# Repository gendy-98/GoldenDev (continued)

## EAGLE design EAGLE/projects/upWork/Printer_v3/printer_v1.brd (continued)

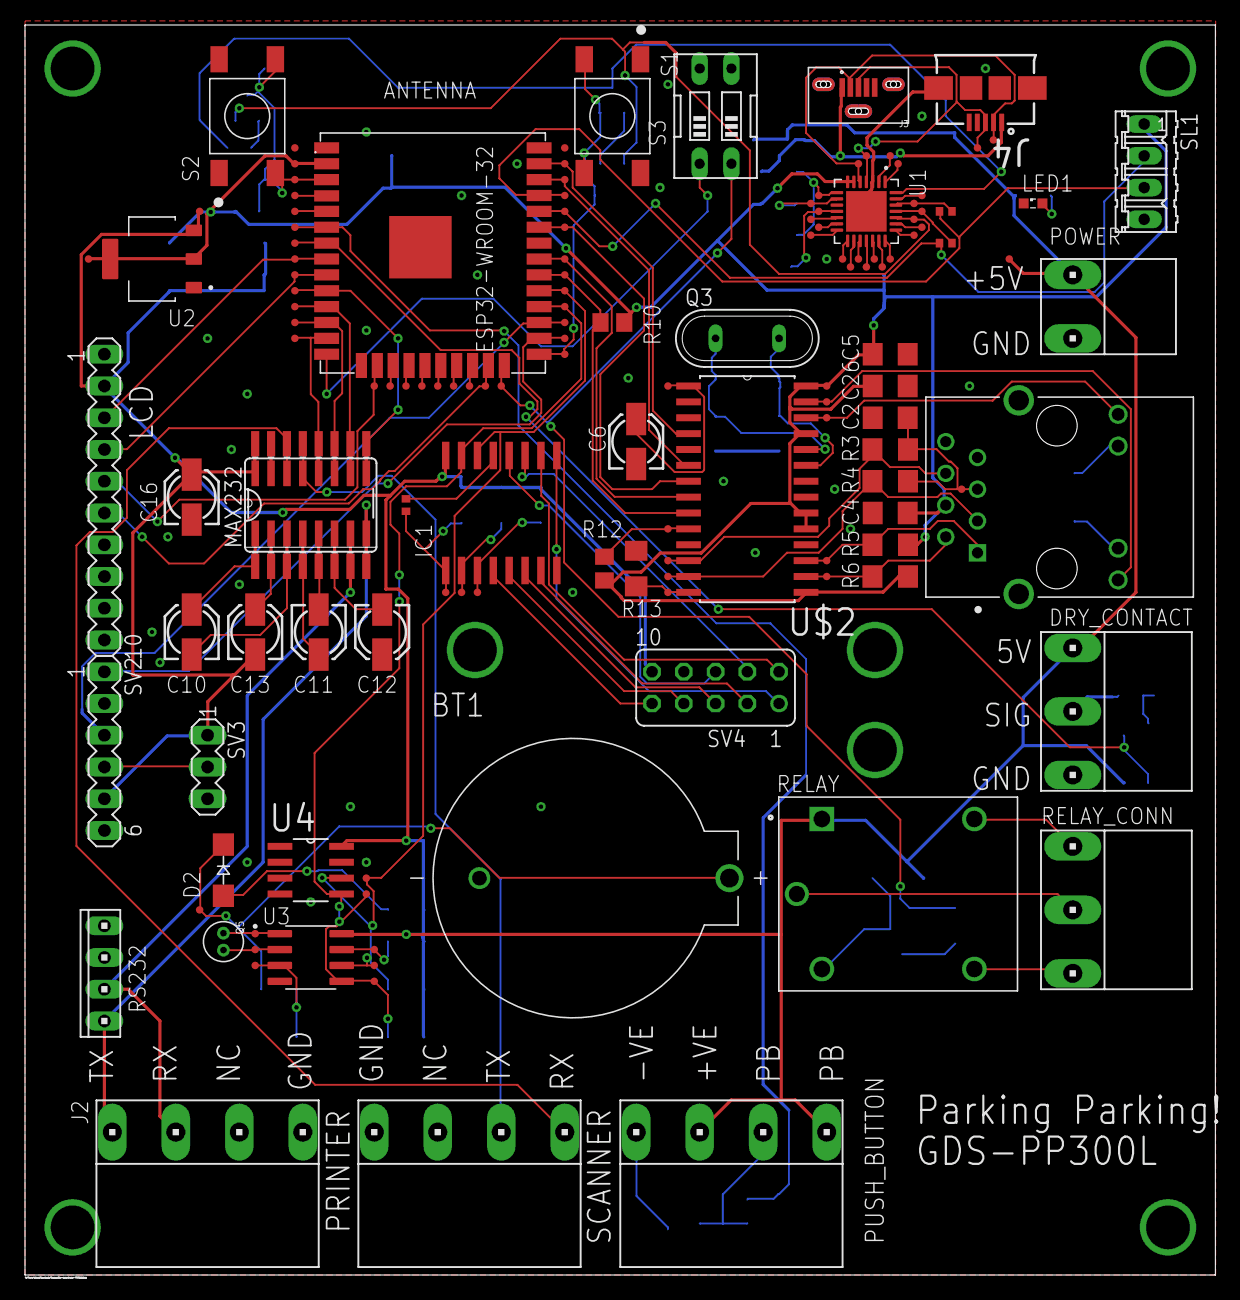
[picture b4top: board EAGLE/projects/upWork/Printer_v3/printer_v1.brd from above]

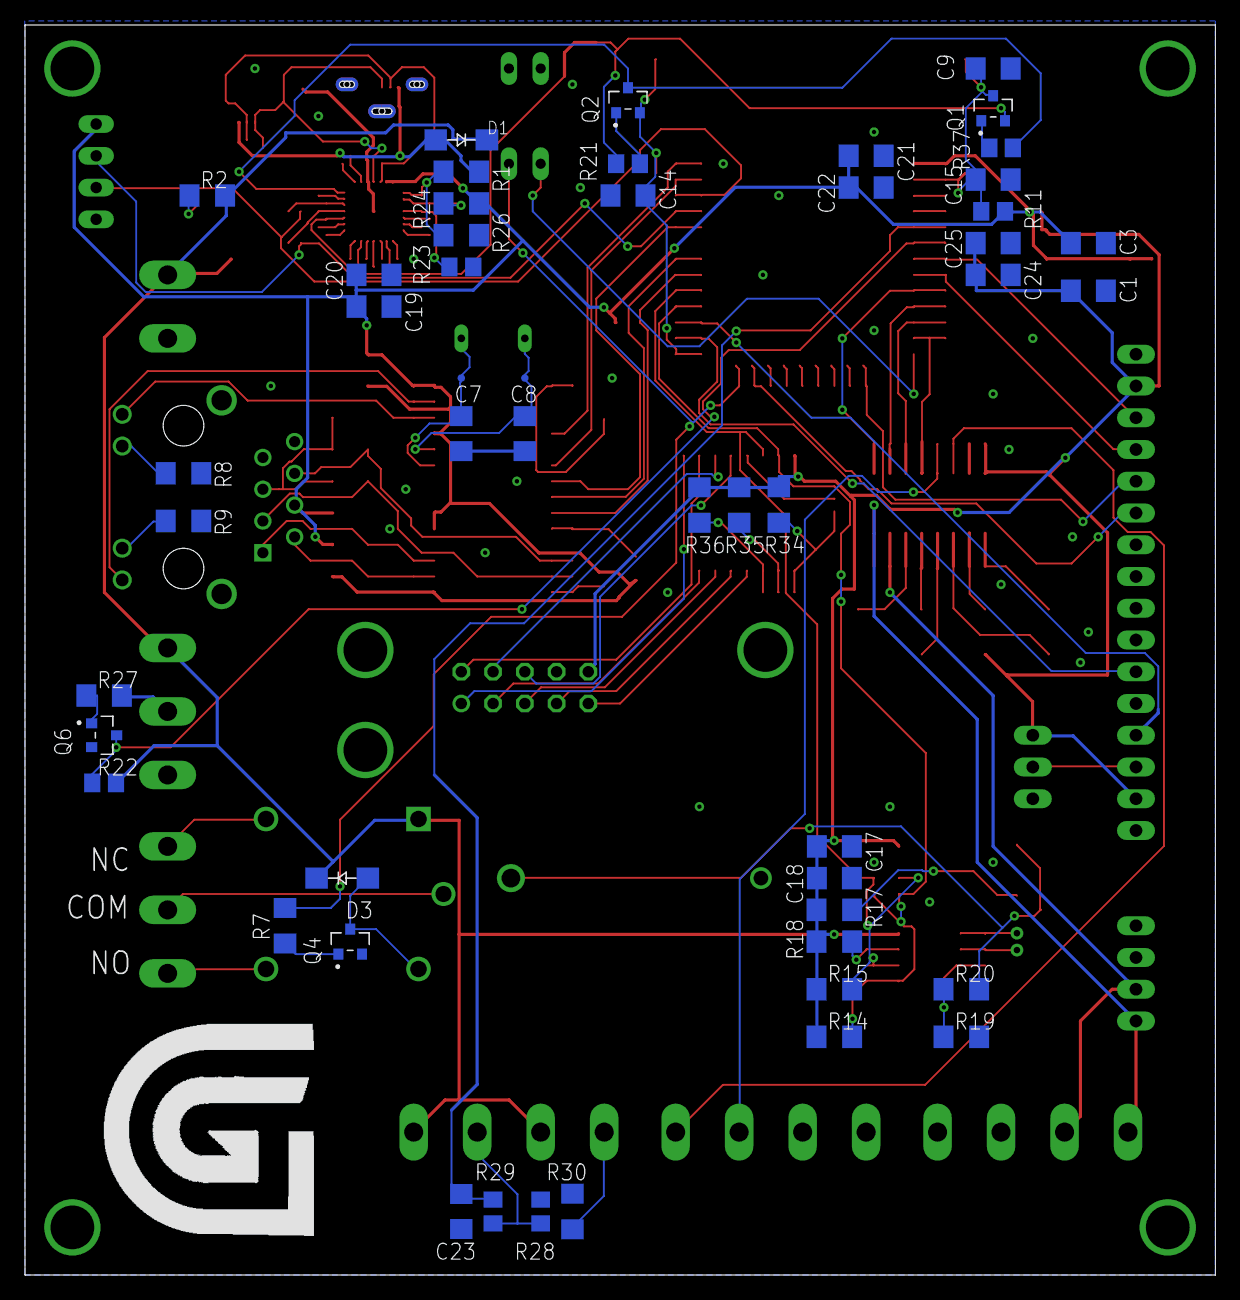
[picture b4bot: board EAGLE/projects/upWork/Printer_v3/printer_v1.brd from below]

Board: 2 copper layers, 95.2 x 100.0 mm, 188 parts (49 on the bottom side), 116 nets.

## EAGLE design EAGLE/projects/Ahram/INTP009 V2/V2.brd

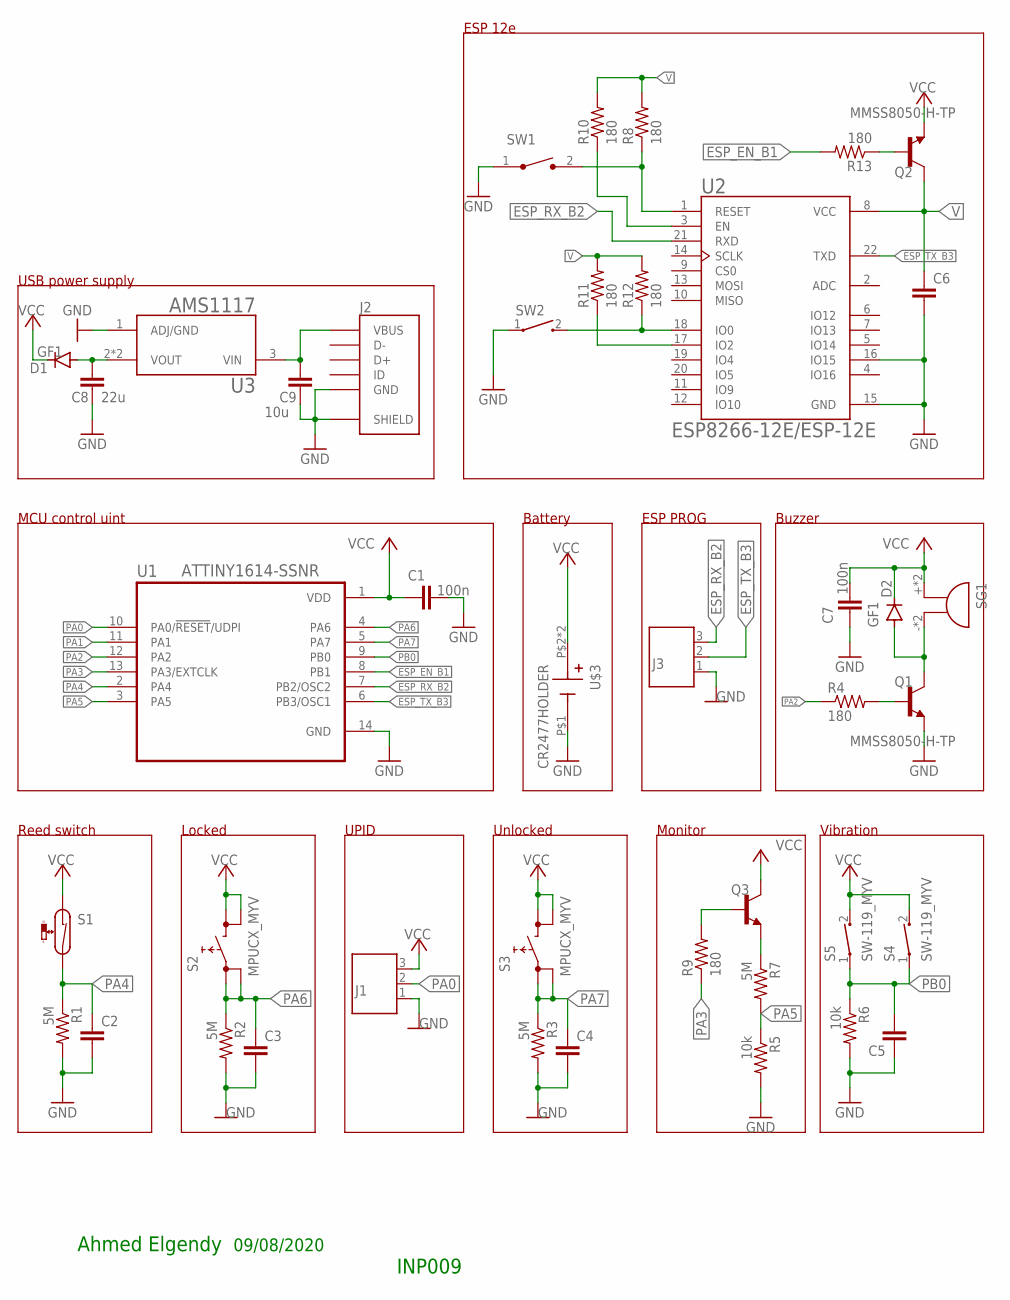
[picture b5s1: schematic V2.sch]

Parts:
C1, C7: 100n; C0805K
C2, C3, C4, C5, C6: C-EUC0805K; C0805K
C8: 22u; C0805K
C9: 10u; C0805K
D1, D2: GF1; SMA-DO214AC
J1, J3: 691508110303
J2: USB3065-XX-00-A_REVE; GCT_USB3065-XX-00-A_REVE
Q1, Q2, Q3: MMSS8050-H-TP; TRANS_MMSS8050-H-TP
R1, R2, R3, R7: 5M; M0805
R4, R8, R9, R10, R11, R12, R13: 180; M0805
R5, R6: 10k; M0805
S1: RI80SMDM-MYV; RI80SMDM-0510-J1
S2, S3: MPUCX_MYV
S4, S5: SW-119_MYV; SW-119
SG1: CMI-9653S-SMT; SMD_BUZZER
SW1: FSMSM; TE_FSMSM
SW2: 1437566-3; SW_1437566-3
U1: ATTINY1614-SSNR; SOIC127P600X175-14N
U2: ESP8266-12E/ESP-12E; XCVR_ESP8266-12E/ESP-12E
U3: AMS1117; SOT229P700X180-4N
U$3: CR2477HOLDER; CR2477

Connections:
ESP_EN_B1: R13.2, U1.8 (PB1)
ESP_RX_B2: J3.3, U1.7 (PB2/OSC2), U2.21 (RXD)
ESP_TX_B3: J3.2, U1.6 (PB3/OSC1), U2.22 (TXD)
GND: C1.2, C2.2, C3.2, C4.2, C5.1, C6.2, C7.1, C8.1, C9.1, J1.1, J2.5 (GND), J2.6 (SHIELD), J2.7 (SHIELD), J2.8 (SHIELD), J2.9 (SHIELD), J3.1, Q1.2 (E), R1.2, R2.2, R3.2, R5.2, R6.2, SW1.1, SW2.1, U1.14 (GND), U2.15 (GND), U2.16 (IO15), U3.1 (ADJ/GND), U$3.P$1 (-)
unnamed: D2.A, Q1.3 (C), SG1.-, SG1.-- (-)
unnamed: C9.2, J2.1 (VBUS), U3.3 (VIN)
unnamed: Q1.1 (B), R4.2
unnamed: C8.2, D1.A, U3.2 (VOUT), U3.4 (VOUT)
unnamed: Q3.1 (B), R9.2
unnamed: Q2.1 (B), R13.1
unnamed: R12.1, SW2.2, U2.18 (IO0)
unnamed: R11.1, U2.17 (IO2)
unnamed: R10.1, U2.3 (EN)
unnamed: R8.1, SW1.2, U2.1 (RESET)
NS3: Q3.2 (E), R7.1
PA0: J1.2, U1.10 (PA0/!RESET!/UDPI)
PA1: U1.11 (PA1)
PA2: R4.1, U1.12 (PA2)
PA3: R9.1, U1.13 (PA3/EXTCLK)
PA4: C2.1, R1.1, S1.P$2 (2), U1.2 (PA4)
PA5: R5.1, R7.2, U1.3 (PA5)
PA6: C3.1, R2.1, S2.1, S2.2, U1.4 (PA6)
PA7: C4.1, R3.1, S3.1, S3.2, U1.5 (PA7)
PB0: C5.2, R6.1, S4.1, S5.1, U1.9 (PB0)
V: C6.1, Q2.3 (C), R8.2, R10.2, R11.2, R12.2, U2.8 (VCC)
VCC: C1.1, C7.2, D1.K (C), D2.K (C), J1.3, Q2.2 (E), Q3.3 (C), S1.P$1 (1), S2.3, S2.4, S3.3, S3.4, S4.2, S5.2, SG1.+, SG1.++ (+), U1.1 (VDD), U$3.P$2 (+), U$3.P$3 (+)

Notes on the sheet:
Ahmed Elgendy
09/08/2020
INP009
MCU control uint
Reed switch
Locked
Unlocked
Battery
Vibration
Buzzer
Monitor
UPID
USB power supply
ESP 12e
ESP PROG

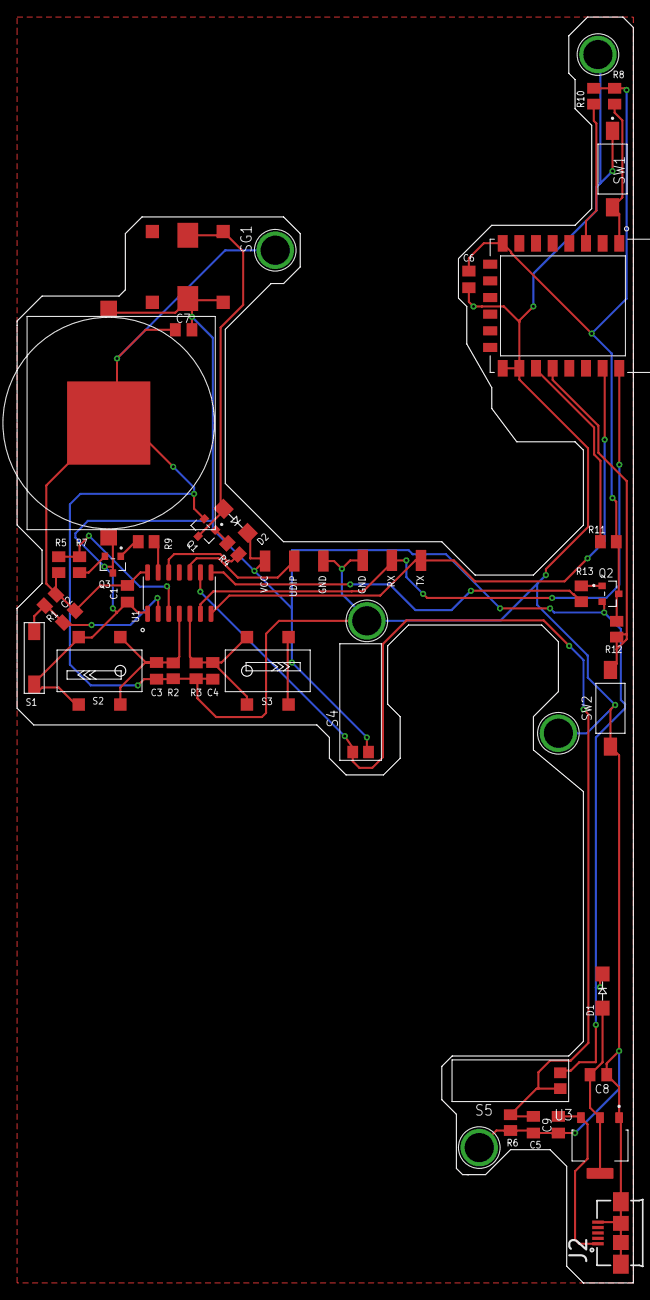
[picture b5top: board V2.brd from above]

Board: 2 copper layers, 74.0 x 152.0 mm, 42 parts (0 on the bottom side), 25 nets.

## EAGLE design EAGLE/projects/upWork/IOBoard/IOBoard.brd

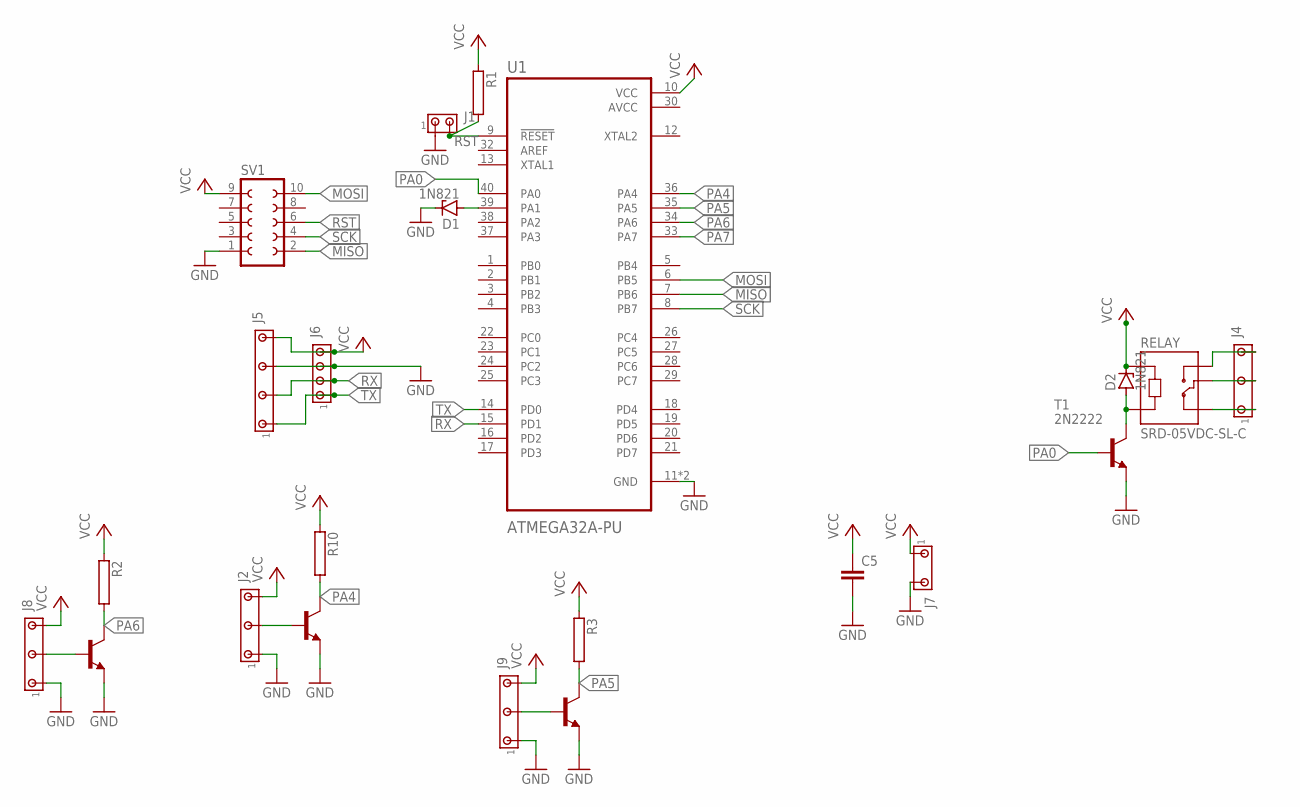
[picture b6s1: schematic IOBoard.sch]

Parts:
C5: C-EU025-024X044; C025-024X044
D1, D2: 1N821; DO35Z10
J1: MTA02-100; 10X02MTA
J2, J4, J8, J9: MTA05-156_MYVSPACE1; 10X05MTA_MYV
J5: MTA07-100_MYV; 10X07MTA_MYV
J6: MTA04-100; 10X04MTA
J7: MTA03-100_MYV; 10X03MTA_MYV
R1, R2, R3, R10: RHPS58; HPS58
RELAY: SRD-05VDC-SL-C; RELAY_SRD-05VDC-SL-C
SV1: FE05-2_MYV; FE05-2
T1, T2, T5, T6: 2N2222; TO18
U1: ATMEGA32A-PU; DIP1540W47P254L5320H635Q40B

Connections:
AVCC: U1.30 (AVCC)
GND: C5.2, D1.C, J1.1, J2.1, J5.5, J6.3, J7.3, J8.1, J9.1, SV1.1, T1.1 (E), T2.1 (E), T5.1 (E), T6.1 (E), U1.11 (GND), U1.31 (GND)
MISO: SV1.2, U1.7 (PB6)
MOSI: SV1.10, U1.6 (PB5)
unnamed: J4.5, RELAY.NO
unnamed: J4.3, RELAY.COM
unnamed: J4.1, RELAY.NC
unnamed: D2.A, RELAY.A2, T1.3 (C)
unnamed: J8.3, T5.2 (B)
unnamed: J2.3, T2.2 (B)
unnamed: J9.3, T6.2 (B)
PA0: T1.2 (B), U1.40 (PA0)
PA1: D1.A, U1.39 (PA1)
PA4: R10.2, T2.3 (C), U1.36 (PA4)
PA5: R3.2, T6.3 (C), U1.35 (PA5)
PA6: R2.2, T5.3 (C), U1.34 (PA6)
PA7: U1.33 (PA7)
RST: J1.2, R1.2, SV1.6, U1.9 (!RESET)
RX: J5.3, J6.2, U1.15 (PD1)
SCK: SV1.4, U1.8 (PB7)
TX: J5.1, J6.1, U1.14 (PD0)
VCC: C5.1, D2.C, J2.5, J5.7, J6.4, J7.1, J8.5, J9.5, R1.1, R2.1, R3.1, R10.1, RELAY.A1, SV1.9, U1.10 (VCC)

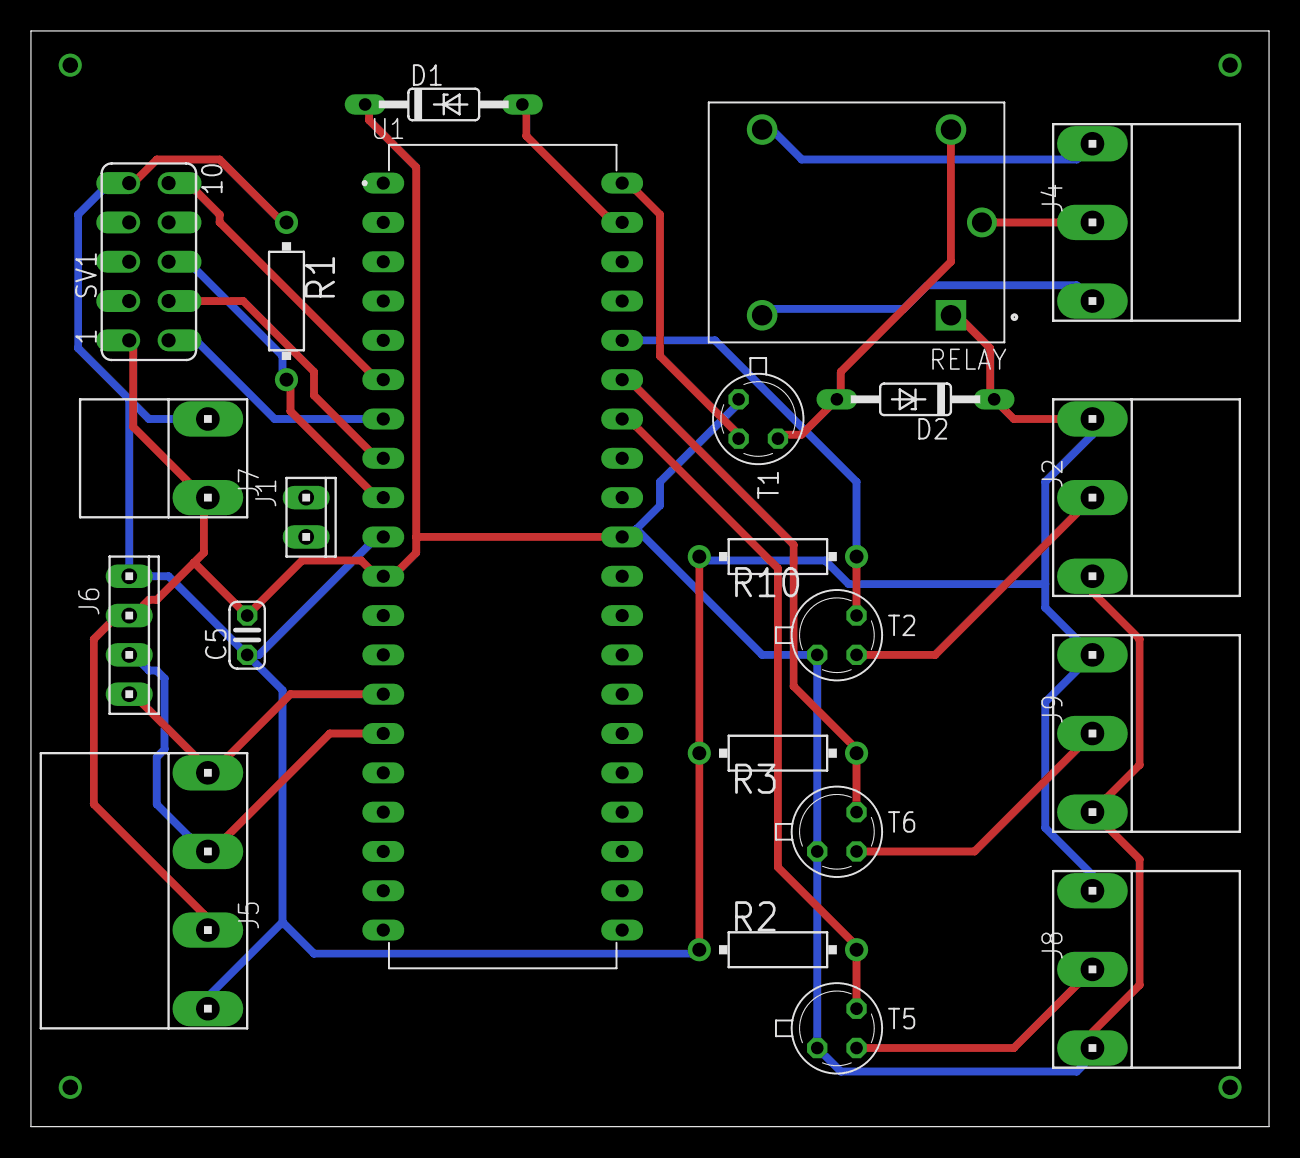
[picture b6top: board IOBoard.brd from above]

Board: 2 copper layers, 80.0 x 70.8 mm, 22 parts (0 on the bottom side), 20 nets.

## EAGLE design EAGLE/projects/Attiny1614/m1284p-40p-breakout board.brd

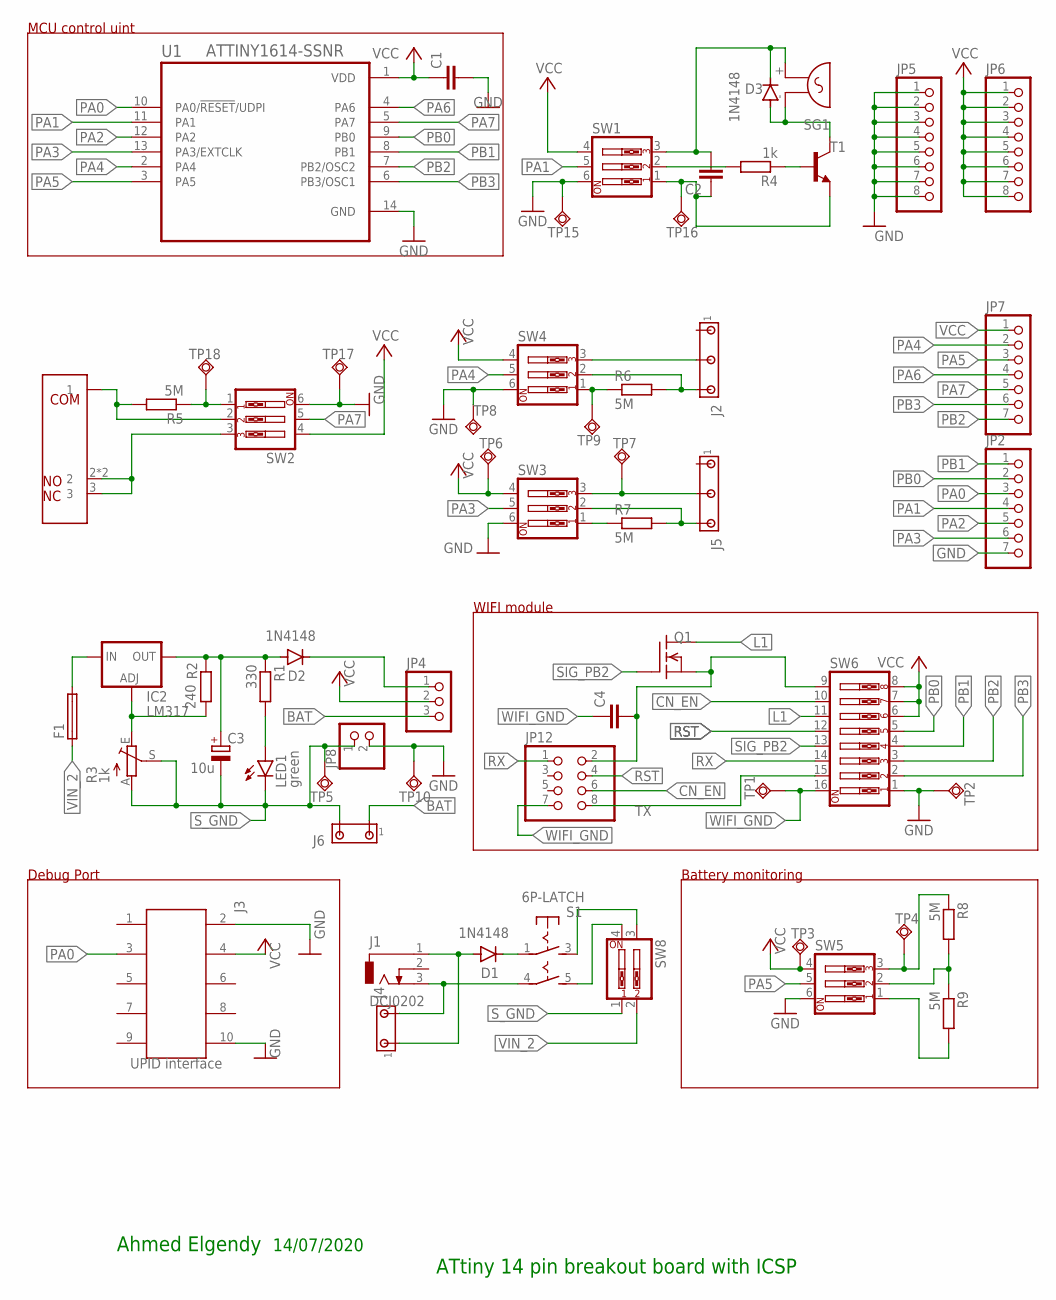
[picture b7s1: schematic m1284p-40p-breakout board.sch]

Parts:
C1, C2, C4: C-EU025-030X050; C025-030X050
C3: 10u; E2-4
D1, D2, D3: 1N4148; DO35-7
F1: SH22,5A
IC2: LM317; 317TS
J1: DCJ0202
J2, J5: MTA05-156_MYVSPACE1; 10X05MTA_MYV
J3: UPID interface; 612010235121
J4, J6: MTA03-100_MYV; 10X03MTA_MYV
JP2, JP7: PINHD-1X7; 1X07
JP4: PINHD-1X3; 1X03
JP5, JP6: PINHD-1X8; 1X08
JP8: PINHD-1X2; 1X02
JP12: PINHD-2X4; 2X04
LED1: green; LED3MM
Q1: BSS295; TO92
R1: 330; 0204/7
R2: 240; 0204/7
R3: 1k; RJ9W
R4: 1k; 0204/7
R5, R6, R7, R8, R9: 5M; 0204/7
S1: 6P-LATCH; TACT-6P-LATCH
S2: REED_1513; REED_MYV
SG1: F/QMX
SW1, SW2, SW3, SW4, SW5: SW_DIP-3; EDG-03
SW6: SW_DIP-8; EDG-08
SW8: SW_DIP-2; EDG-02
T1: 2N2222; TO18
TP1, TP2, TP3, TP4, TP5, TP6, TP7, TP8, TP9, TP10, TP15, TP16, TP17, TP18: TPSQPAD1-13; P1-13
U1: ATTINY1614-SSNR; SOIC127P600X175-14N

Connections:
BAT: J6.1, JP4.3
CN_EN: JP12.6, SW6.10
GND: C1.2, J3.2, J3.10, JP2.7, JP5.1, JP5.2, JP5.3, JP5.4, JP5.5, JP5.6, JP5.7, JP5.8, JP8.2, SW1.6, SW2.6, SW3.6, SW4.6, SW5.6, SW6.1, TP2.TP, TP8.TP, TP10.TP, TP15.TP, TP17.TP, U1.14 (GND)
L1: Q1.3 (D), SW6.11
unnamed: D1.C, S1.1
unnamed: C3.+, D2.A, IC2.2 (OUT), R1.1, R2.2
unnamed: D1.A, J1.1, J4.1
unnamed: LED1.A, R1.2
unnamed: R4.1, T1.2 (B)
unnamed: IC2.1 (ADJ), R2.1, R3.E
unnamed: J1.3, J4.3, S1.4 (3)
unnamed: F1.2, IC2.3 (IN)
unnamed: J2.5, R6.2, SW4.2
unnamed: R4.2, SW1.2
unnamed: R5.2, S2.1, SW2.2
unnamed: R8.2, R9.1, SW5.2
unnamed: S1.5 (4), SW8.4
unnamed: R9.2, SW5.1
unnamed: R5.1, SW2.1, TP18.TP
unnamed: J2.3, SW4.3
unnamed: R6.1, SW4.1, TP9.TP
unnamed: D2.C, JP4.1
unnamed: C2.2, D3.C, SG1.+ (2), SW1.3
unnamed: C2.1, SW1.1, T1.1 (E), TP16.TP
unnamed: S2.2, S2.3, S2.4 (2), SW2.3
unnamed: R8.1, SW5.3, TP4.TP
unnamed: R7.1, SW3.1
unnamed: D3.A, SG1.- (1), T1.3 (C)
unnamed: J5.5, R7.2, SW3.2
unnamed: J5.3, SW3.3, TP7.TP
unnamed: C4.2, JP12.2, Q1.1 (S), SW6.9
PA0: J3.3, JP2.3, U1.10 (PA0/!RESET!/UDPI)
PA1: JP2.4, SW1.5, U1.11 (PA1)
PA2: JP2.5, U1.12 (PA2)
PA3: JP2.6, SW3.5, U1.13 (PA3/EXTCLK)
PA4: JP7.2, SW4.5, U1.2 (PA4)
PA5: JP7.3, SW5.5, U1.3 (PA5)
PA6: JP7.4, U1.4 (PA6)
PA7: JP7.5, SW2.5, U1.5 (PA7)
PB0: JP2.2, SW6.5, U1.9 (PB0)
PB1: JP2.1, SW6.4, U1.8 (PB1)
PB2: JP7.7, SW6.3, U1.7 (PB2/OSC2)
PB3: JP7.6, SW6.2, U1.6 (PB3/OSC1)
RST: JP12.4, SW6.12
RX: JP12.1, SW6.14
SIG_PB2: Q1.2 (G), SW6.13
S_GND: C3.-, J6.3, JP8.1, LED1.K (C), R3.A, R3.S, SW8.1, TP5.TP
TX: JP12.8, SW6.15
VCC: C1.1, J3.4, JP4.2, JP6.1, JP6.2, JP6.3, JP6.4, JP6.5, JP6.6, JP6.7, JP6.8, JP7.1, SW1.4, SW2.4, SW3.4, SW4.4, SW5.4, SW6.6, SW6.7, SW6.8, TP3.TP, TP6.TP, U1.1 (VDD)
VIN_1: S1.3 (2), SW8.3
VIN_2: F1.1, SW8.2
WIFI_GND: C4.1, JP12.7, SW6.16, TP1.TP

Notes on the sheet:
Ahmed Elgendy
14/07/2020
ATtiny 14 pin breakout board with ICSP
MCU control uint
Debug Port
WIFI module
Battery monitoring

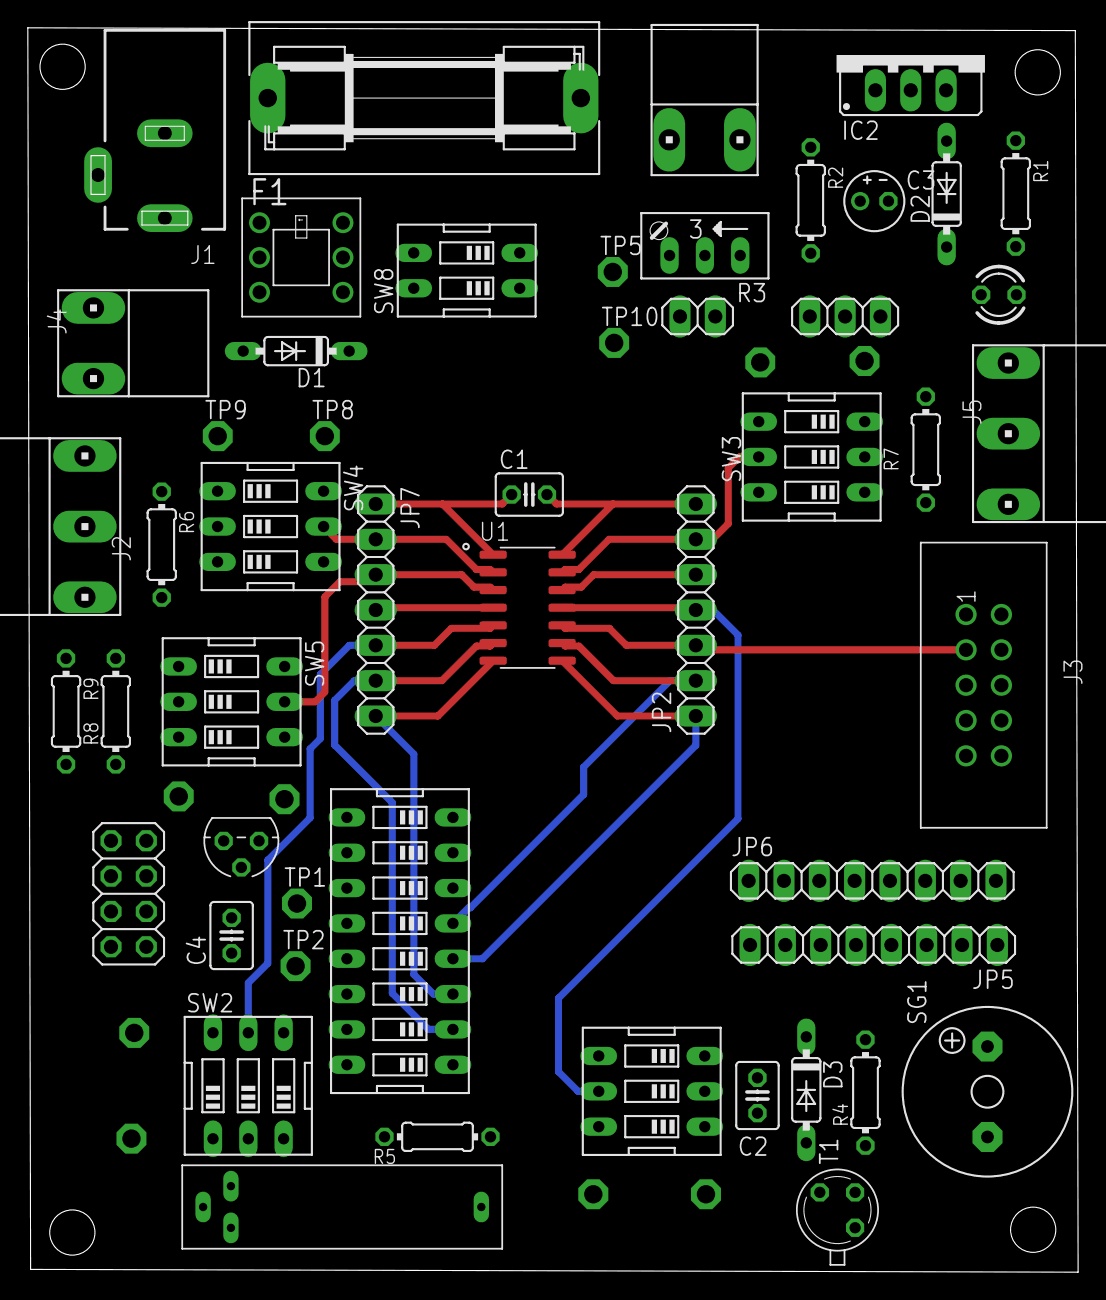
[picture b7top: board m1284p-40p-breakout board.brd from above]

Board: 2 copper layers, 75.5 x 89.4 mm, 59 parts (0 on the bottom side), 52 nets.

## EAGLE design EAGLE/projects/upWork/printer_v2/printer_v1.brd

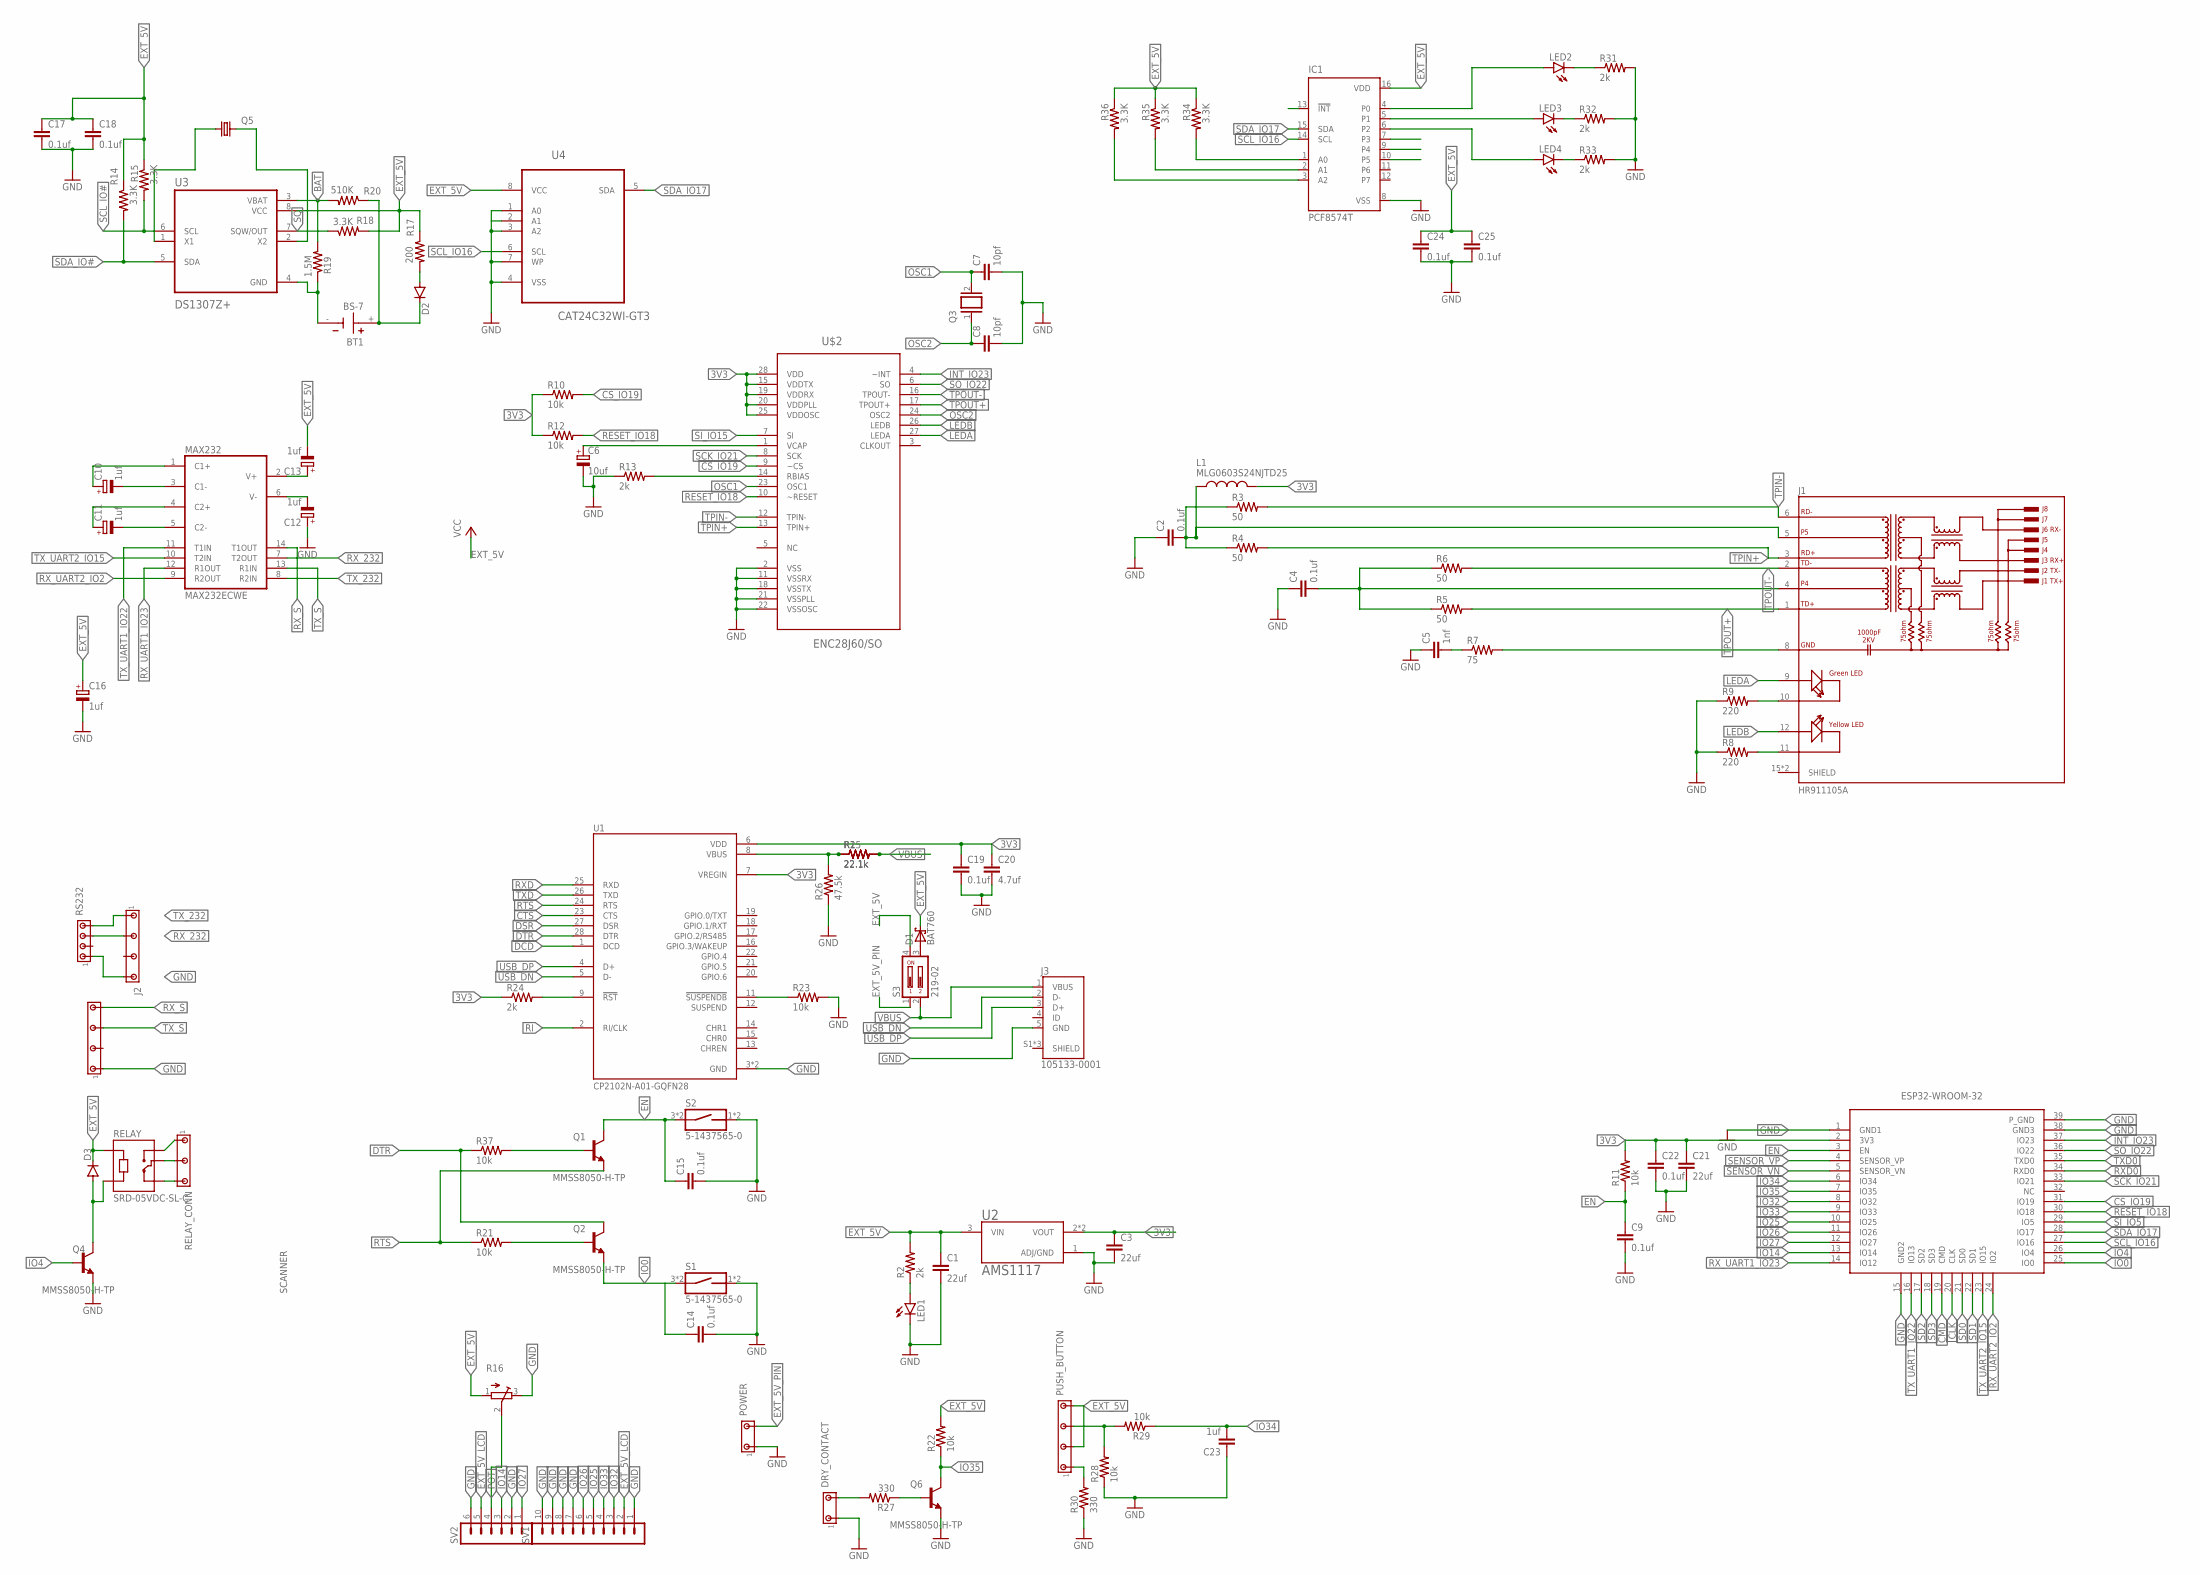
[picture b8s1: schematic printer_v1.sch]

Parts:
BT1: BS-7; BAT_BS-7
C1, C3, C21: 22uf; C0603
C2, C4, C9, C14, C15, C17, C18, C19, C22, C24, C25: 0.1uf; C0402
C5: 1nf; C0402
C6: 10uf; 153CLV-0405
C7, C8: 10pf; C0402
C10, C11, C12, C13, C16: 1uf; A/3216-18R
C20: 4.7uf; C0402
C23: 1uf; C0603
D1: BAT760; SOD323(F)
D2, D3: DIODE-DO-214AC; DO-214AC
DRY_CONTACT: MTA03-100_MYV; 10X03MTA_MYV
IC1: PCF8574T; SO16W
J1: HR911105A; HANRUN_HR911105A
J2: MTA07-100_MYV; 10X07MTA_MYV
J3: 105133-0001; MOLEX_105133-0001
L1: MLG0603S24NJTD25; INDC0603X33N
LED1, LED2, LED3, LED4: LEDSML0603; SML0603
MAX232: MAX232ECWE; SO16L
POWER: MTA03-100_MYV; 10X03MTA_MYV
PUSH_BUTTON: MTA07-100_MYV; 10X07MTA_MYV
Q1, Q2, Q4, Q6: MMSS8050-H-TP; TRANS_MMSS8050-H-TP
Q3: XTAL/S; QS
Q5: KX-327-NHF; 3.2X1.5
R1, R25: 22.1k; R0402
R2, R13, R24, R31, R32, R33: 2k; R0402
R3, R4, R5, R6: 50; R0402
R7: 75; R0402
R8, R9: 220; R0402
R10, R11, R12, R21, R22, R23, R28, R29, R37: 10k; R0402
R14, R15, R18, R34, R35, R36: 3.3K; R0603
R16: TRIM_EU-3223G; 3223G
R17: 200; R0603
R19: 1.5M; R0603
R20: 510K; R0603
R26: 47.5k; R0402
R27, R30: 330; R0402
RELAY: SRD-05VDC-SL-C; RELAY_SRD-05VDC-SL-C
RELAY_CONN: MTA05-156_MYVSPACE1; 10X05MTA_MYV
RS232: MTA04-100; 10X04MTA
S1, S2: 5-1437565-0; SW_5-1437565-0
S3: 219-02; CTS-219-02
SCANNER: MTA07-100_MYV; 10X07MTA_MYV
SV1: MA10-1
SV2: MA06-1
U1: CP2102N-A01-GQFN28; QFN50P500X500X80-29N
U2: AMS1117; SOT229P700X180-4N
U3: DS1307Z+; SOIC127P600X175-8N
U4: CAT24C32WI-GT3; SOIC127P600X175-8N
U$1: ESP32-WROOM-32
U$2: ENC28J60/SO; SOIC127P1034X264-28N

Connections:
3V3: C3.1, C19.1, C20.1, C21.1, C22.1, L1.2, R10.1, R11.2, R12.1, R24.1, U1.6 (VDD), U1.7 (VREGIN), U2.2 (VOUT), U2.4 (VOUT), U$1.2 (3V3), U$2.15 (VDDTX), U$2.19 (VDDRX), U$2.20 (VDDPLL), U$2.25 (VDDOSC), U$2.28 (VDD)
BAT: R19.2, R20.2, U3.3 (VBAT)
CLK: U$1.20 (CLK)
CMD: U$1.19 (CMD)
CS_IO19: R10.2, U$1.31 (IO19), U$2.9 (~CS)
CTS: U1.23 (CTS)
DCD: U1.1 (DCD)
DSR: U1.27 (DSR)
DTR: Q2.3 (C), R37.1, U1.28 (DTR)
EN: C9.1, C15.1, Q1.3 (C), R11.1, S2.3 (1), S2.4 (1), U$1.3 (EN)
EXT_5V: C1.1, C13.-, C16.+, C17.1, C18.1, C24.1, C25.1, D1.1 (K), D3.C, IC1.16 (VDD), MAX232.16 (VCC), PUSH_BUTTON.3, PUSH_BUTTON.7, R2.2, R14.1, R15.1, R16.1 (A), R17.1, R18.2, R22.2, R34.1, R35.1, R36.1, RELAY.A1, S3.4, U2.3 (VIN), U3.8 (VCC), U4.8 (VCC)
EXT_5V_LCD: SV1.2, SV2.5
EXT_5V_PIN: POWER.3, S3.1
GND: C1.2, C2.1, C3.2, C4.1, C5.1, C6.-, C7.2, C8.2, C9.2, C12.+, C14.2, C15.2, C16.-, C17.2, C18.2, C19.2, C20.2, C21.2, C22.2, C23.1, C24.2, C25.2, DRY_CONTACT.1, IC1.8 (VSS), J2.7, J3.5 (GND), LED1.C, MAX232.15 (GND), POWER.1, Q4.2 (E), Q6.2 (E), R8.1, R9.1, R13.1, R16.3 (E), R23.2, R26.1, R28.1, R30.1, R31.2, R32.2, R33.2, RS232.1, S1.1 (2), S1.2, S2.1 (2), S2.2, SCANNER.1, SV1.1, SV1.7, SV1.8, SV1.9, SV1.10, SV2.2, SV2.6, U1.3 (GND), U1.29 (GND), U2.1 (ADJ/GND), U4.1 (A0), U4.2 (A1), U4.3 (A2), U4.4 (VSS), U4.7 (WP), U$1.1 (GND1), U$1.15 (GND2), U$1.38 (GND3), U$1.39 (P_GND), U$2.2 (VSS), U$2.11 (VSSRX), U$2.18 (VSSTX), U$2.21 (VSSPLL), U$2.22 (VSSOSC)
INT_IO23: U$1.37 (IO23), U$2.4 (~INT)
IO0: C14.1, Q2.2 (E), S1.3 (1), S1.4 (1), U$1.25 (IO0)
IO4: Q4.1 (B), U$1.26 (IO4)
IO14: SV2.3, U$1.13 (IO14)
IO25: SV1.5, U$1.10 (IO25)
IO26: SV1.6, U$1.11 (IO26)
IO27: SV2.1, U$1.12 (IO27)
IO32: SV1.3, U$1.8 (IO32)
IO33: SV1.4, U$1.9 (IO33)
IO34: C23.2, R29.1, U$1.6 (IO34)
IO35: Q6.3 (C), R22.1, U$1.7 (IO35)
LEDA: J1.9 (GA), U$2.27 (LEDA)
LEDB: J1.12 (YA), U$2.26 (LEDB)
unnamed: LED1.A, R2.1
unnamed: Q1.1 (B), R37.2
unnamed: Q2.1 (B), R21.2
unnamed: R1.1, R25.1, R26.2, U1.8 (VBUS)
unnamed: J1.8 (GND), R7.2
unnamed: R23.1, U1.11 (!SUSPENDB)
unnamed: J1.11 (YC), R8.2
unnamed: C2.2, J1.5, L1.1, R3.1, R4.1
unnamed: J1.10 (GC), R9.2
unnamed: R13.2, U$2.14 (RBIAS)
unnamed: C6.+, U$2.1 (VCAP)
unnamed: C10.+, MAX232.1 (C1+)
unnamed: C5.2, R7.1
unnamed: C10.-, MAX232.3 (C1-)
unnamed: C11.-, MAX232.5 (C2-)
unnamed: R24.2, U1.9 (!RST)
unnamed: C4.2, J1.4, R5.1, R6.1
unnamed: C11.+, MAX232.4 (C2+)
unnamed: C12.-, MAX232.6 (V-)
unnamed: C13.+, MAX232.2 (V+)
unnamed: RELAY.NC, RELAY_CONN.5
unnamed: RELAY.COM, RELAY_CONN.3
unnamed: LED2.C, R31.1
unnamed: Q5.1, U3.1 (X1)
unnamed: RELAY.NO, RELAY_CONN.1
unnamed: D3.A, Q4.3 (C), RELAY.A2
unnamed: D2.A, R17.2
unnamed: BT1.+, D2.C, R20.1
unnamed: BT1.-, R19.1, U3.4 (GND)
unnamed: Q5.2, U3.2 (X2)
unnamed: Q6.1 (B), R27.1
unnamed: PUSH_BUTTON.5, R28.2, R29.2
unnamed: D1.2 (A), S3.3
unnamed: DRY_CONTACT.3, R27.2
unnamed: IC1.4 (P0), LED2.A
unnamed: IC1.5 (P1), LED3.A
unnamed: IC1.6 (P2), LED4.A
unnamed: PUSH_BUTTON.1, R30.2
unnamed: IC1.1 (A0), R34.2
unnamed: IC1.2 (A1), R35.2
unnamed: IC1.3 (A2), R36.2
unnamed: LED3.C, R32.1
unnamed: LED4.C, R33.1
OSC1: C7.1, Q3.2, U$2.23 (OSC1)
OSC2: C8.1, Q3.1, U$2.24 (OSC2)
POT: R16.2 (S), SV2.4
RESET_IO18: R12.2, U$1.30 (IO18), U$2.10 (~RESET)
RI: U1.2 (RI/CLK)
RTS: Q1.2 (E), R21.1, U1.24 (RTS)
RXD: U1.25 (RXD)
RXD0: U$1.34 (RXD0)
RX_232: J2.3, MAX232.7 (T2OUT), RS232.3
RX_S: MAX232.14 (T1OUT), SCANNER.7
RX_UART1_IO23: MAX232.12 (R1OUT), U$1.14 (IO12)
RX_UART2_IO2: MAX232.9 (R2OUT), U$1.24 (IO2)
SCK_IO21: U$1.33 (IO21), U$2.8 (SCK)
SCL_IO16: IC1.14 (SCL), U4.6 (SCL), U$1.27 (IO16)
SCL_IO#: R15.2, U3.6 (SCL)
SD0: U$1.21 (SD0)
SD1: U$1.22 (SD1)
SD2: U$1.17 (SD2)
SD3: U$1.18 (SD3)
SDA_IO17: IC1.15 (SDA), U4.5 (SDA), U$1.28 (IO17)
SDA_IO#: R14.2, U3.5 (SDA)
SENSOR_VN: U$1.5 (SENSOR_VN)
SENSOR_VP: U$1.4 (SENSOR_VP)
SI_IO5: U$1.29 (IO5)
SI_IO15: U$2.7 (SI)
SO_IO22: U$1.36 (IO22), U$2.6 (SO)
SQ: R18.1, U3.7 (SQW/OUT)
TPIN+: J1.3 (RD+), R4.2, U$2.13 (TPIN+)
TPIN-: J1.6 (RD-), R3.2, U$2.12 (TPIN-)
TPOUT+: J1.1 (TD+), R5.2, U$2.17 (TPOUT+)
TPOUT-: J1.2 (TD-), R6.2, U$2.16 (TPOUT-)
TXD: U1.26 (TXD)
TXD0: U$1.35 (TXD0)
TX_232: J2.1, MAX232.8 (R2IN), RS232.4
TX_S: MAX232.13 (R1IN), SCANNER.5
TX_UART1_IO22: MAX232.11 (T1IN), U$1.16 (IO13)
TX_UART2_IO15: MAX232.10 (T2IN), U$1.23 (IO15)
USB_DN: J3.2 (D-), U1.5 (D-)
USB_DP: J3.3 (D+), U1.4 (D+)
VBUS: J3.1 (VBUS), R1.2, R25.2, S3.2
